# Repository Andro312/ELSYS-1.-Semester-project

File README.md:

# Innovation project for Electronic system design and innovation

This git is my part of our group project to use sensors with arduino IDE, send that data to a website.

I've been whole responsible to design a breakout board suitable to the ESP32 mikrokontroller.
The circuit board have been made with NTNUs manufacturing capabilities in mind, 
and have therefore all connection at the bottom of the board.

I've also combines all the individual codes and made them work together.

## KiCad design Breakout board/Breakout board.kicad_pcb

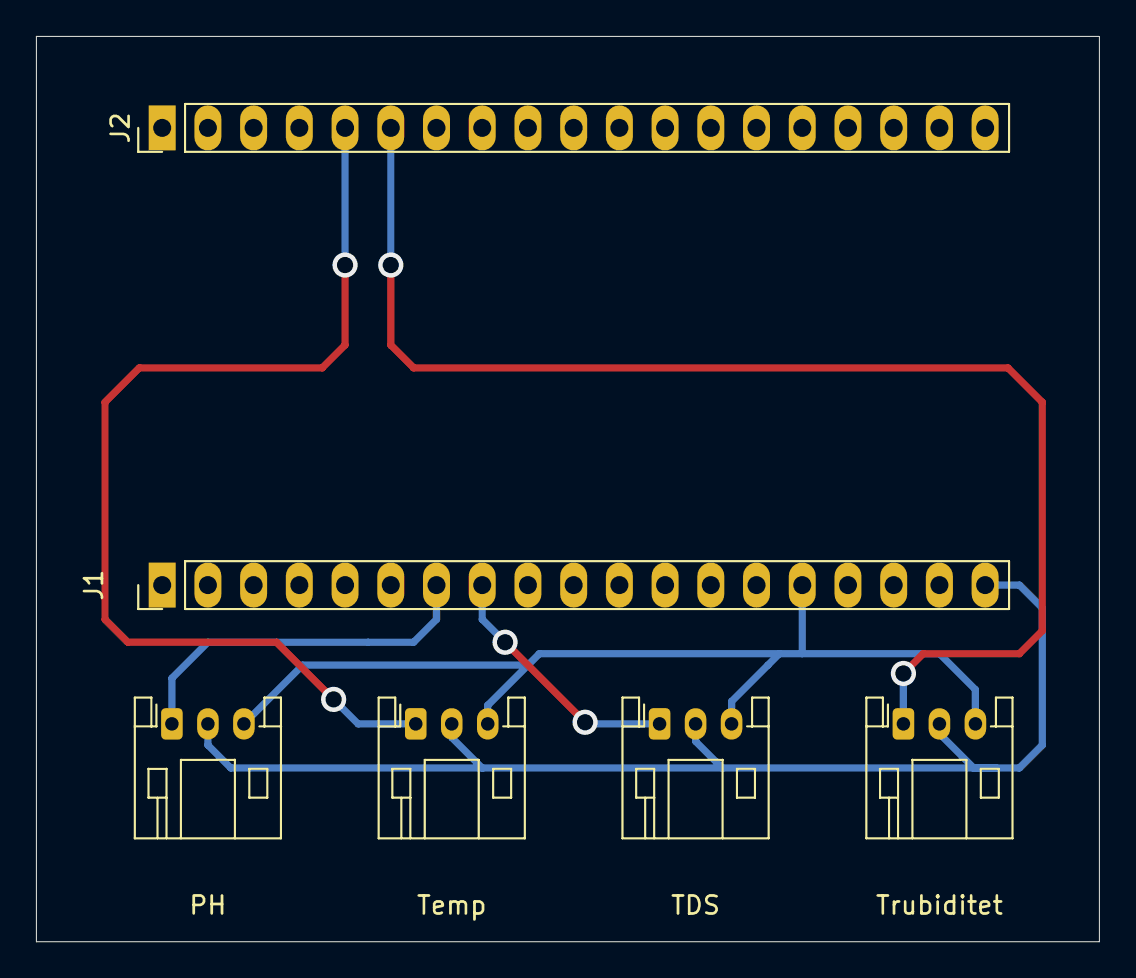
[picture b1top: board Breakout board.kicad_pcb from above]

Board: 2 copper layers, 59.1 x 50.3 mm, 6 parts (0 on the bottom side), 6 nets.

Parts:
J1, J2: Conn_01x19; PinHeader_1x19_P2.54mm_Vertical
PH: Conn_01x03; JST_PH_S3B-PH-K_1x03_P2.00mm_Horizontal
TDS: Conn_01x03; JST_PH_S3B-PH-K_1x03_P2.00mm_Horizontal
Temp: Conn_01x03; JST_PH_S3B-PH-K_1x03_P2.00mm_Horizontal
Trubiditet: Conn_01x03; JST_PH_S3B-PH-K_1x03_P2.00mm_Horizontal

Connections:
unnamed: J1.19 (5V), PH.2, TDS.2, Temp.2, Trubiditet.2
unnamed: J1.15 (GND), PH.3, TDS.3, Temp.3, Trubiditet.3
unnamed: J1.7 (GPIO_32), PH.1
unnamed: J2.6 (GPIO_00), Trubiditet.1
unnamed: J2.5 (GPIO_02), Temp.1
unnamed: J1.8 (GPIO_33), TDS.1

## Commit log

2024-12-25 Added Files from ELSYS GK project
